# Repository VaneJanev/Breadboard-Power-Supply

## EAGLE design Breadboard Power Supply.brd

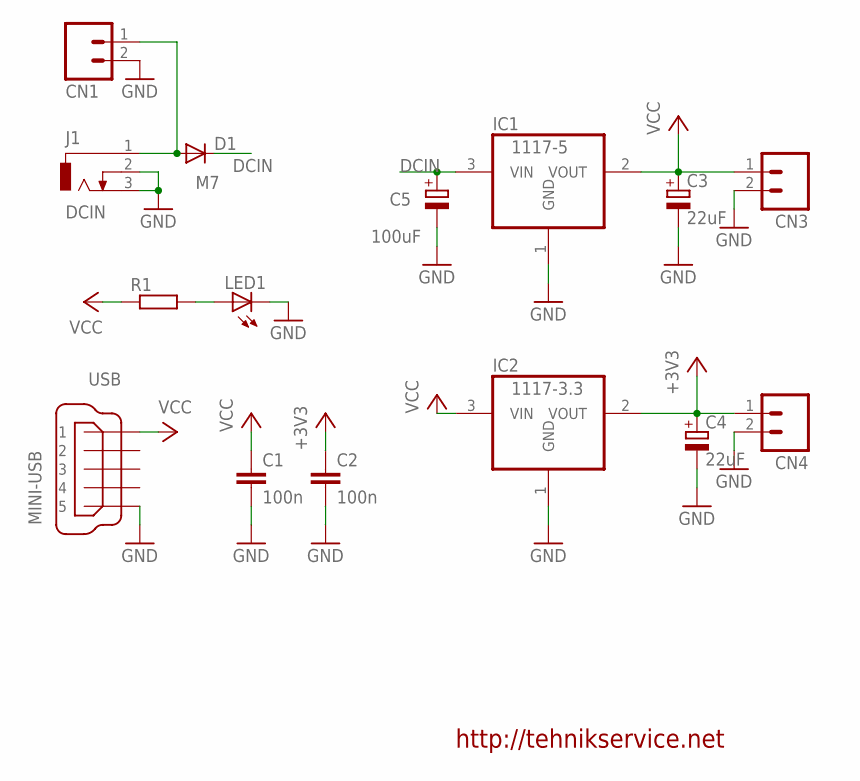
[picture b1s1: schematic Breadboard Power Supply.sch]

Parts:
C1, C2: 100n; C0805
C3, C4: 22uF; E2,5-5
C5: 100uF; E2,5-5
CN1, CN3, CN4: M02; 02P
D1: M7; DO-214AC
IC1: 1117-5; SOT223
IC2: 1117-3.3; SOT223
J1: DCIN; DCJ0202
LED1: LEDCHIPLED_0805; CHIPLED_0805
R1: R-EU_R0805; R0805
USB: MINI-USB; 32005-201

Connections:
+3V3: C2.1, C4.+, CN4.1, IC2.2 (VOUT)
DCIN: C5.+, D1.C, IC1.3 (VIN)
GND: C1.2, C2.2, C3.-, C4.-, C5.-, CN1.2, CN3.2, CN4.2, IC1.1 (GND), IC2.1 (GND), J1.2, J1.3, LED1.C, USB.5
unnamed: LED1.A, R1.2
unnamed: CN1.1, D1.A, J1.1
VCC: C1.1, C3.+, CN3.1, IC1.2 (VOUT), IC2.3 (VIN), R1.1, USB.1

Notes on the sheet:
http://tehnikservice.net

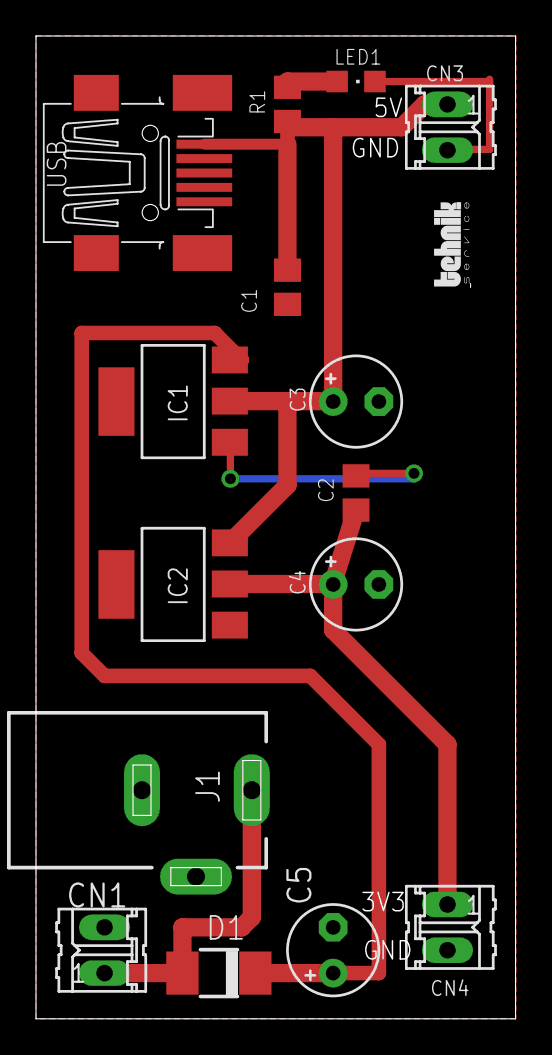
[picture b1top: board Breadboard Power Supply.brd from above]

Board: 2 copper layers, 26.6 x 54.6 mm, 16 parts (0 on the bottom side), 6 nets.

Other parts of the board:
U$1: LOGOT

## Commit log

2015-06-03 :tada: Added .gitattributes
2015-06-03 Breadboard Power Supply
